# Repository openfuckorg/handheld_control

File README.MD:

OpenFuck Wiki https://github.com/openfuckorg/documents/wiki

This is a handheld control module /box for the OpenFUCK (or really anything you care to plug it into).
Designed by the awesome @RuthlessRachel (via FetLife) :D

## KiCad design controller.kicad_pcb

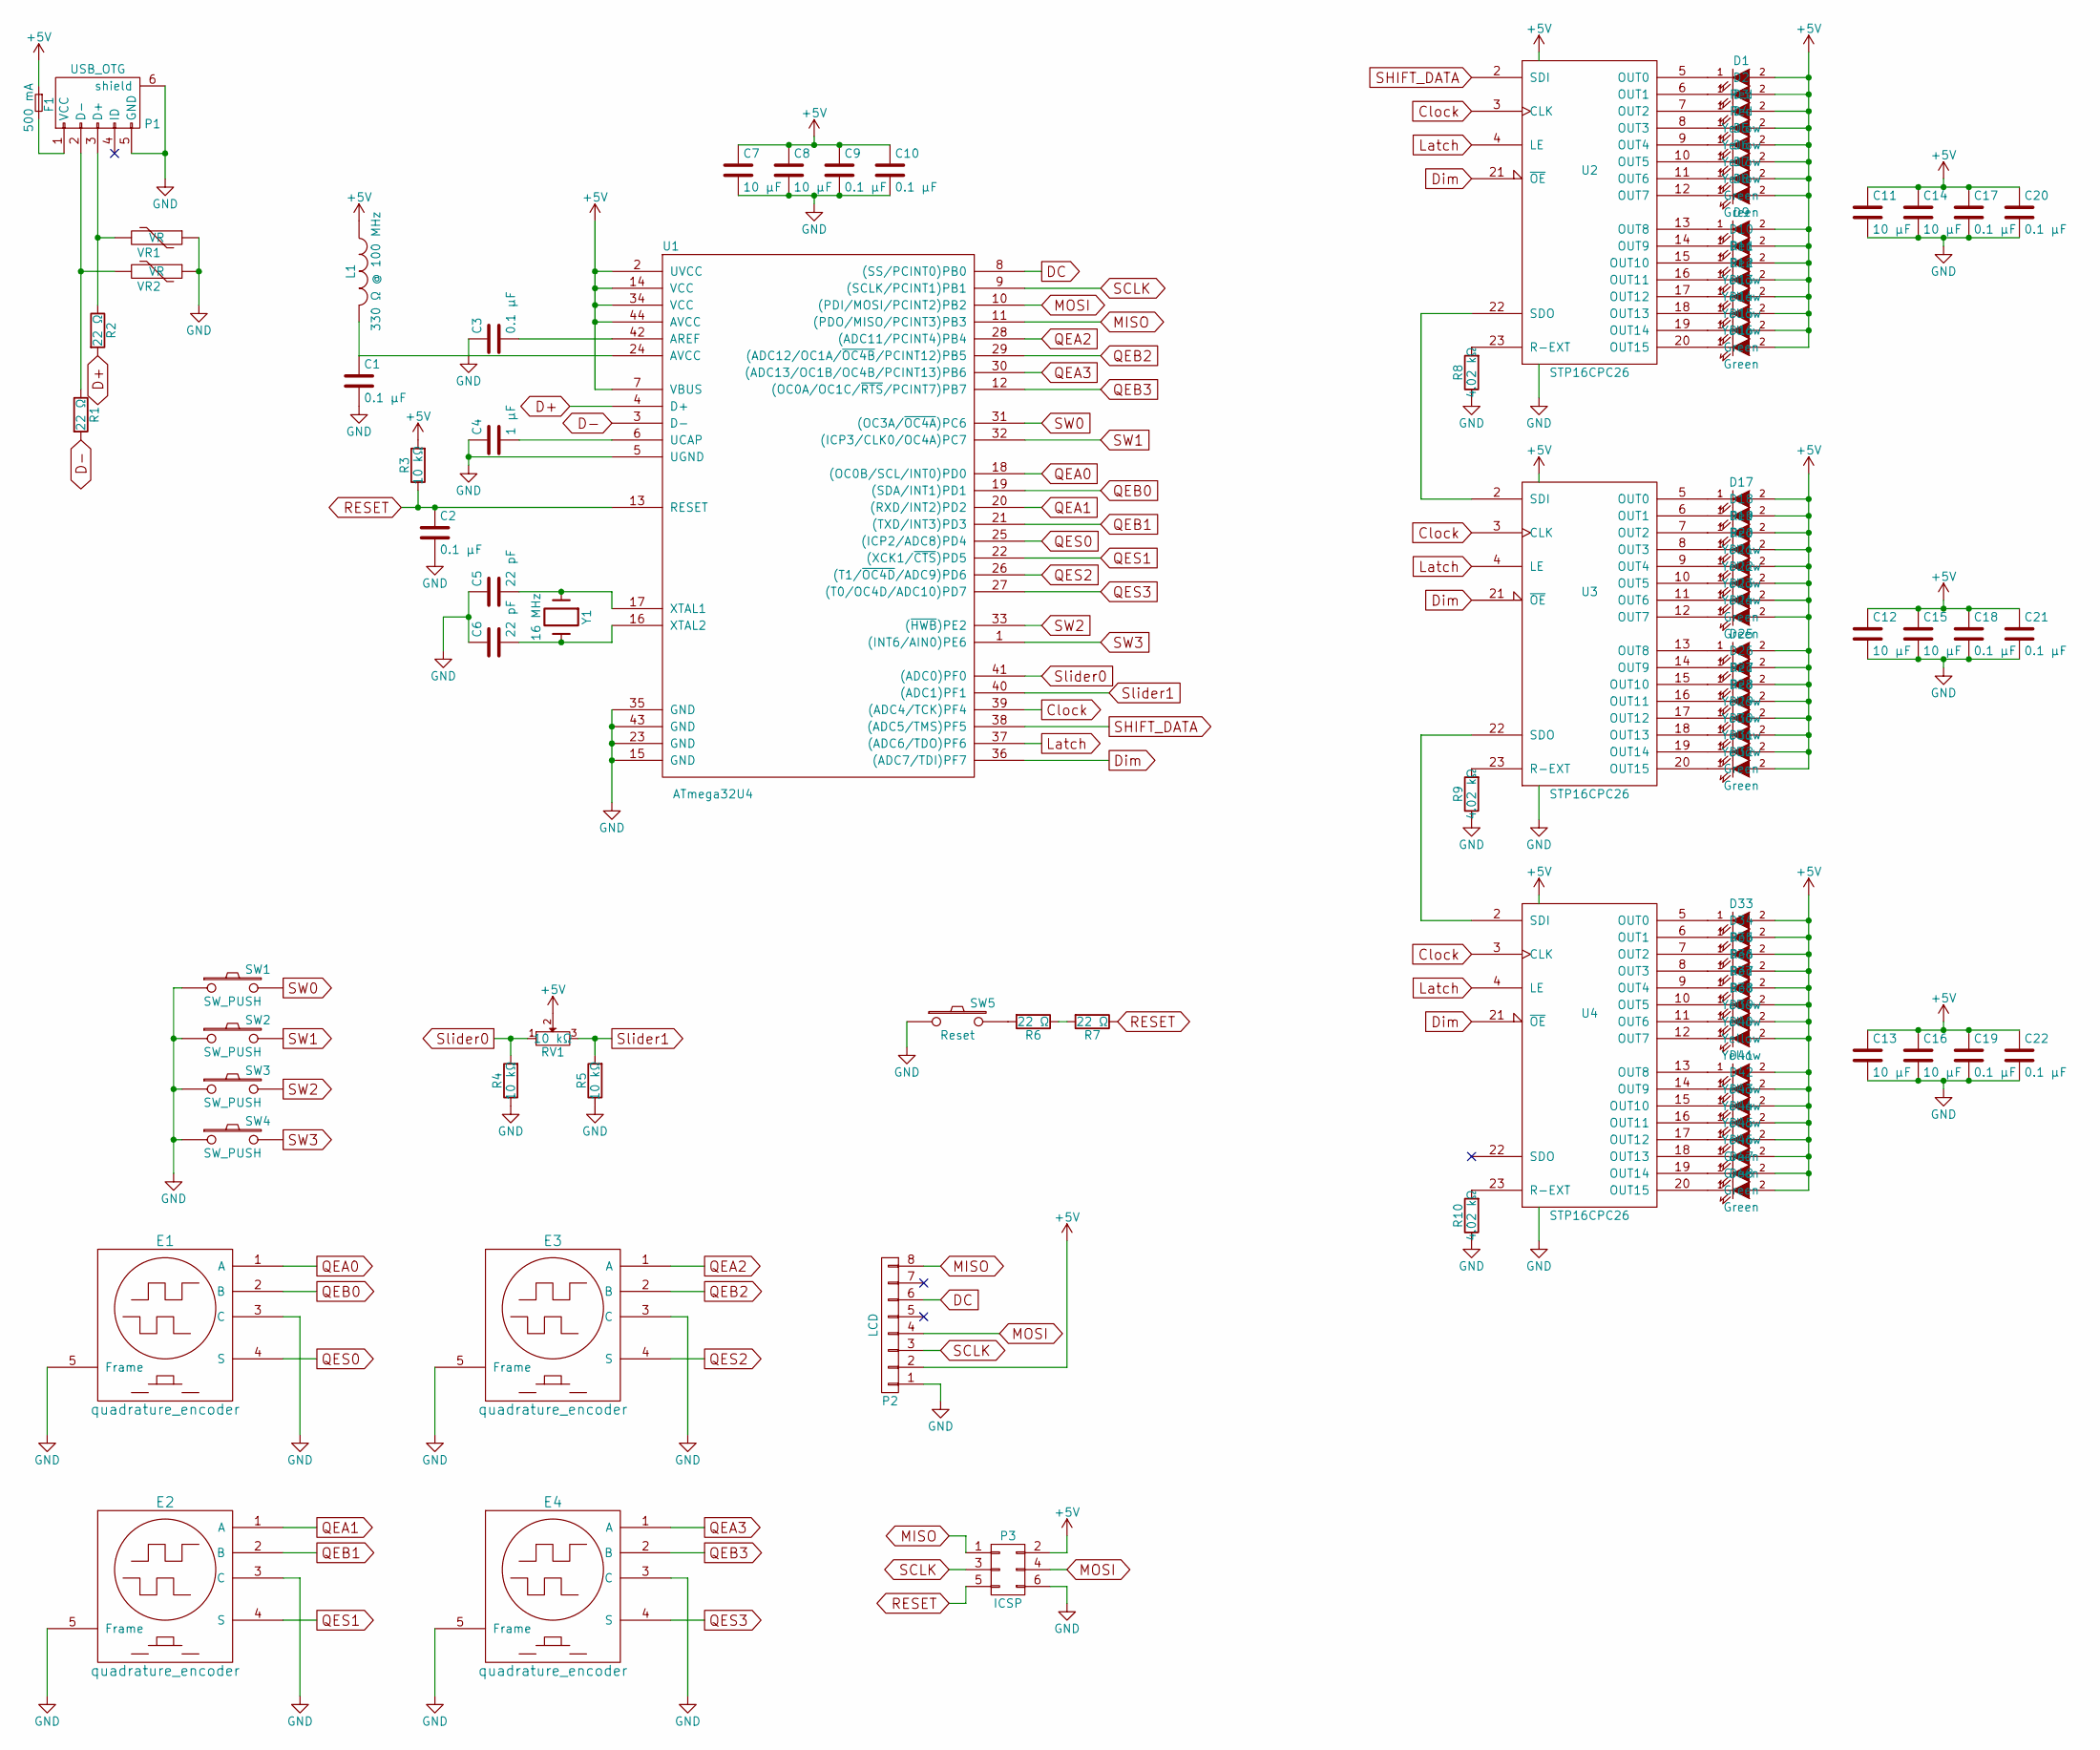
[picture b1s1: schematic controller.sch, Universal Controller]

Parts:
C1, C2, C3, C9, C10, C17, C18, C19, C20, C21, C22: 0.1 μF; C_0805_HandSoldering
C4: 1 μF; C_0805_HandSoldering
C5, C6: 22 pF; C_0805_HandSoldering
C7, C8, C11, C12, C13, C14, C15, C16: 10 μF; C_0805_HandSoldering
D1, D2, D9, D10, D17, D18, D25, D26, D33, D34, D35, D36: Red; LED_0603
D3, D4, D5, D6, D11, D12, D13, D14, D19, D20, D21, D22, D27, D28, D29, D30, D37, D38, D39, D40, D41, D42, D43, D44: Yellow; LED_0603
D7, D8, D15, D16, D23, D24, D31, D32, D45, D46, D47, D48: Green; LED_0603
E1, E2, E3, E4: quadrature_encoder; eve-vcgjl016b
F1: 500 mA; R_1812_HandSoldering
L1: 330 Ω @ 100 MHz; R_0805_HandSoldering
P1: USB_OTG; USB_Micro-B_10103594-0001LF
P2: LCD; 2.4_lcd
P3: ICSP; Pin_Header_Straight_2x03
R1, R2, R6, R7: 22 Ω; R_0805_HandSoldering
R3, R4, R5: 10 kΩ; R_0805_HandSoldering
R8, R9, R10: 4.02 kΩ; R_0805_HandSoldering
RV1: 10 kΩ; bourns-pta6043_60mm-slide-pot
SW1, SW2, SW3, SW4: SW_PUSH; SW_SPST_B3S-1000
SW5: Reset; SW_SPST_B3S-1000
U1: ATmega32U4; TQFP-44_10x10mm_Pitch0.8mm
U2, U3, U4: STP16CPC26; TSSOP-24_4.4x7.8mm_Pitch0.65mm
VR1, VR2: VR; R_0603_HandSoldering
Y1: 16 MHz; abls7m2_crystal

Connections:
+5V: C7.1, C8.1, C9.1, C10.1, C11.1, C12.1, C13.1, C14.1, C15.1, C16.1, C17.1, C18.1, C19.1, C20.1, C21.1, C22.1, D1.2 (A), D2.2 (A), D3.2 (A), D4.2 (A), D5.2 (A), D6.2 (A), D7.2 (A), D8.2 (A), D9.2 (A), D10.2 (A), D11.2 (A), D12.2 (A), D13.2 (A), D14.2 (A), D15.2 (A), D16.2 (A), D17.2 (A), D18.2 (A), D19.2 (A), D20.2 (A), D21.2 (A), D22.2 (A), D23.2 (A), D24.2 (A), D25.2 (A), D26.2 (A), D27.2 (A), D28.2 (A), D29.2 (A), D30.2 (A), D31.2 (A), D32.2 (A), D33.2 (A), D34.2 (A), D35.2 (A), D36.2 (A), D37.2 (A), D38.2 (A), D39.2 (A), D40.2 (A), D41.2 (A), D42.2 (A), D43.2 (A), D44.2 (A), D45.2 (A), D46.2 (A), D47.2 (A), D48.2 (A), F1.1, L1.1, P2.2, P3.2, R3.2, RV1.2, U1.2 (UVCC), U1.7 (VBUS), U1.14 (VCC), U1.34 (VCC), U1.44 (AVCC), U2.24 (VDD), U3.24 (VDD), U4.24 (VDD)
Clock: U1.39 ((ADC4/TCK)PF4), U2.3 (CLK), U3.3 (CLK), U4.3 (CLK)
D+: R2.2, U1.4 (D+)
D-: R1.2, U1.3 (D-)
DC: P2.6, U1.8 ((SS/PCINT0)PB0)
Dim: U1.36 ((ADC7/TDI)PF7), U2.21 (~OE), U3.21 (~OE), U4.21 (~OE)
Latch: U1.37 ((ADC6/TDO)PF6), U2.4 (LE), U3.4 (LE), U4.4 (LE)
MISO: P2.8, P3.1, U1.11 ((PDO/MISO/PCINT3)PB3)
MOSI: P2.4, P3.4, U1.10 ((PDI/MOSI/PCINT2)PB2)
unnamed: C3.2, U1.42 (AREF)
unnamed: C4.2, U1.6 (UCAP)
unnamed: C5.2, U1.17 (XTAL1), Y1.1
unnamed: C6.2, U1.16 (XTAL2), Y1.2
unnamed: D1.1 (K), U2.5 (OUT0)
unnamed: D2.1 (K), U2.6 (OUT1)
unnamed: D3.1 (K), U2.7 (OUT2)
unnamed: D4.1 (K), U2.8 (OUT3)
unnamed: D5.1 (K), U2.9 (OUT4)
unnamed: D6.1 (K), U2.10 (OUT5)
unnamed: D7.1 (K), U2.11 (OUT6)
unnamed: D8.1 (K), U2.12 (OUT7)
unnamed: D9.1 (K), U2.13 (OUT8)
unnamed: D10.1 (K), U2.14 (OUT9)
unnamed: D11.1 (K), U2.15 (OUT10)
unnamed: D12.1 (K), U2.16 (OUT11)
unnamed: D13.1 (K), U2.17 (OUT12)
unnamed: D14.1 (K), U2.18 (OUT13)
unnamed: D15.1 (K), U2.19 (OUT14)
unnamed: D16.1 (K), U2.20 (OUT15)
unnamed: D17.1 (K), U3.5 (OUT0)
unnamed: D18.1 (K), U3.6 (OUT1)
unnamed: D19.1 (K), U3.7 (OUT2)
unnamed: D20.1 (K), U3.8 (OUT3)
unnamed: D21.1 (K), U3.9 (OUT4)
unnamed: D22.1 (K), U3.10 (OUT5)
unnamed: D23.1 (K), U3.11 (OUT6)
unnamed: D24.1 (K), U3.12 (OUT7)
unnamed: D25.1 (K), U3.13 (OUT8)
unnamed: D26.1 (K), U3.14 (OUT9)
unnamed: D27.1 (K), U3.15 (OUT10)
unnamed: D28.1 (K), U3.16 (OUT11)
unnamed: D29.1 (K), U3.17 (OUT12)
unnamed: D30.1 (K), U3.18 (OUT13)
unnamed: D31.1 (K), U3.19 (OUT14)
unnamed: D32.1 (K), U3.20 (OUT15)
unnamed: D33.1 (K), U4.5 (OUT0)
unnamed: D34.1 (K), U4.6 (OUT1)
unnamed: D35.1 (K), U4.7 (OUT2)
unnamed: D36.1 (K), U4.8 (OUT3)
unnamed: D37.1 (K), U4.9 (OUT4)
unnamed: D38.1 (K), U4.10 (OUT5)
unnamed: D39.1 (K), U4.11 (OUT6)
unnamed: D40.1 (K), U4.12 (OUT7)
unnamed: D41.1 (K), U4.13 (OUT8)
unnamed: D42.1 (K), U4.14 (OUT9)
unnamed: D43.1 (K), U4.15 (OUT10)
unnamed: D44.1 (K), U4.16 (OUT11)
unnamed: D45.1 (K), U4.17 (OUT12)
unnamed: D46.1 (K), U4.18 (OUT13)
unnamed: D47.1 (K), U4.19 (OUT14)
unnamed: D48.1 (K), U4.20 (OUT15)
unnamed: F1.2, P1.1 (VCC)
unnamed: P1.2 (D-), R1.1, VR2.2
unnamed: P1.3 (D+), R2.1, VR1.2
unnamed: R6.1, R7.2
unnamed: R6.2, SW5.2
unnamed: R8.2, U2.23 (R-EXT)
unnamed: R9.2, U3.23 (R-EXT)
unnamed: R10.2, U4.23 (R-EXT)
unnamed: U2.22 (SDO), U3.2 (SDI)
unnamed: U3.22 (SDO), U4.2 (SDI)
QEA0: E1.1 (A), U1.18 ((OC0B/SCL/INT0)PD0)
QEA1: E2.1 (A), U1.20 ((RXD/INT2)PD2)
QEA2: E3.1 (A), U1.28 ((ADC11/PCINT4)PB4)
QEA3: E4.1 (A), U1.30 ((ADC13/OC1B/OC4B/PCINT13)PB6)
QEB0: E1.2 (B), U1.19 ((SDA/INT1)PD1)
QEB1: E2.2 (B), U1.21 ((TXD/INT3)PD3)
QEB2: E3.2 (B), U1.29 ((ADC12/OC1A/~OC4B~/PCINT12)PB5)
QEB3: E4.2 (B), U1.12 ((OC0A/OC1C/~RTS~/PCINT7)PB7)
QES0: E1.4 (S), U1.25 ((ICP2/ADC8)PD4)
QES1: E2.4 (S), U1.22 ((XCK1/~CTS~)PD5)
QES2: E3.4 (S), U1.26 ((T1/~OC4D~/ADC9)PD6)
QES3: E4.4 (S), U1.27 ((T0/OC4D/ADC10)PD7)
RESET: C2.1, P3.5, R3.1, R7.1, U1.13 (RESET)
SCLK: P2.3, P3.3, U1.9 ((SCLK/PCINT1)PB1)
SHIFT_DATA: U1.38 ((ADC5/TMS)PF5), U2.2 (SDI)
SW0: SW1.2, U1.31 ((OC3A/~OC4A~)PC6)
SW1: SW2.2, U1.32 ((ICP3/CLK0/OC4A)PC7)
SW2: SW3.2, U1.33 ((~HWB~)PE2)
SW3: SW4.2, U1.1 ((INT6/AIN0)PE6)
Slider0: R4.2, RV1.1, U1.41 ((ADC0)PF0)
Slider1: R5.2, RV1.3, U1.40 ((ADC1)PF1)

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
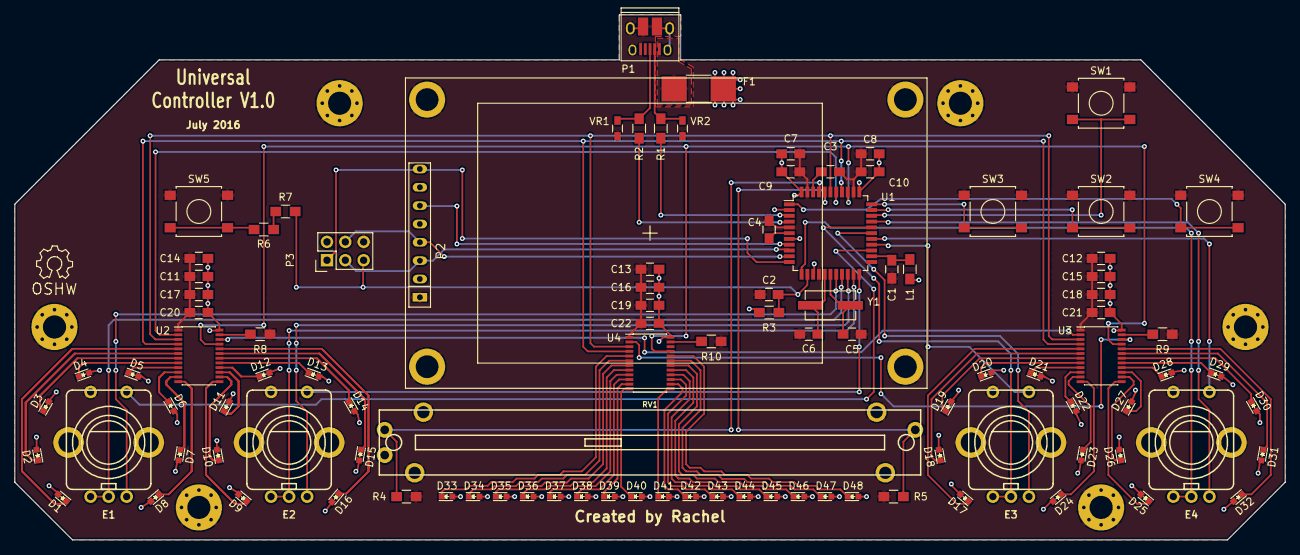
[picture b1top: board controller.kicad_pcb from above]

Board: 2 copper layers, 176.0 x 72.8 mm, 102 parts (0 on the bottom side), 94 nets.

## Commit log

2016-11-22 Moved shit to org ownership
